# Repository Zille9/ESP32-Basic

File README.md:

# ESP32-Basic with FabGL VGA library + PS2-Keyboard
### Basic32+ with FabGL VGA library + PS2 PS2Controller for VGA monitor output - 2019 - 2023       
#### Ursprungsversion von: Rob Cai <rocaj74@gmail.com>
#### erweitert/modifiziert von:Reinhard Zielinski <zille09@gmail.com>                                                                   
#### Das Ergebnis ist ein kleiner Retro-Computer mit folgender Ausstattung:
- (Schaltplan siehe Ordner Schematic) 

## Hardware:
```
-ESP32 / 240MHz
-56472 Basic Bytes free
-VGA-Display 320x240 Pixel 64 Farben , AV (IO26) oder TFT-Screen 320x240 Pixel
-IO-Erweiterung mit MCP23017 (2x8 IO-Ports) + EEPROM 512kB 
-CardKb als PS2-Tastatur nutzbar (siehe Ordner <src/CardKeyBoard_neu>)
-Unterstützung von externem SPI-RAM 128kB, 512kB (Adafruit SPI-Fram) oder 2, 4 oder 8 MB PSRAM im SPI-Mode
-PS2-Keyboard 
-RTC DS3231 
-SD-Card
```

## Software:
```
Die Ursprungsversion wurde durch folgende Funktionen erweitert  

-fliesskomma Arithmetik
-Grafikfunktionen 	
-mathematische Funktionen 	
-Stringfunktionen 	
-lange Variablennamen  	
-viele zusätzliche Befehle (DATA,READ,STRG$,LEFT$,RIGHT$,MID$,POS,TAB,SPC,SIN,COS,TAN,ATN,LOG,SQR,PI usw.) 	
-erweiterte logische Operatoren (AND, OR) 	
-BIT-Manipulation &,|,%,<<,>> usw. 	
-Klammerrechnung 	
-IF THEN ELSE Abfragen 	
-Speichermonitor 	
-Exponential-Ein/Ausgabe 	
-Verschiedene Sensoren und Komponenten HC-S04, Dallas DS18S20, DHT, LCD, Neopixel-LED, BMP180 	
-Zeileneditor 
-BMP-Bilddatei-Import / Export
-Spritefunktionen (noch in der Entwicklung)
-Soundfunktionen (noch in der Entwicklung)
-integrierte Kurzhilfe
-Binärprogramme können mit RUN"/xxx.bin" gestartet werden - siehe Ordner <Software>

```

***Special Thanks on Guido Lehwalder and Marcelo Dantas ->RUN-CPM is a great Work!***

***Also thanks on Fabrizio Di Vittorio for the excellent FabGl-Library***

```
-Startbildschirm
```

```
-Basic-Befehle
```

```
-Basic -Funktionen
```

```
-Programm Globus.Bas
```

```
-Darstellung einer BMP-Datei
```

```
-Programmlisting
```

```
Screenshot als BMP-Datei exportiert
```

```
...mit RUN kann dann auch CPM gestartet werden.
```

```
...RUN-CPM Startbildschirm , mit EXIT kehrt man wieder zum Basic32+ zurück.
```

```
...der GRID-Befehl in Aktion .
```

## Bibliotheken einbinden und Basic32+ compilieren:
```
-die im Ordner libraries liegenden Unterverzeichnisse ins Arduino libraries-Verzeichnis kopieren

-zusätzlich die FabGL-lib mit dem Bibliotheksmanager der Arduino-IDE installieren

-die Quellen befinden sich im Ordner "src/FabGL-Basic" ->kompilieren und in den ESP32 laden

-den Inhalt des Verzeichnisses SD-Card auf eine SD-Karte kopieren .... und mit ESP32+Basic loslegen :-)

Im Ordner RUN-CPM befindet sich die um den OTA-Loader erweiterte Variante, um nach Eingabe von EXIT wieder zum Basic zurückzukehren.
```

## Komponenten:

-ESP32 NodeMCU https://www.berrybase.de/esp32-nodemcu-development-board?sPartner=g_shopping&gclid=EAIaIQobChMI-fTJwNmx_wIVkupRCh1mTAgZEAQYBSABEgKjwvD_BwE

-MCP23017 https://www.reichelt.de/i-o-erweiterung-16bit-1-8-5v-seriell-i2c-dip-28-mcp-23017-e-sp-p140074.html?&trstct=pos_0&nbc=1

-FRAM 512kB https://www.adafruit.com/product/4719

-SD-Card Modul https://www.reichelt.de/arduino-sd-karten-modul-ard-module-sd-p282683.html?PROVID=2788&gclid=EAIaIQobChMIqL3-sdqx_wIVQ9rVCh1oSQiAEAQYAiABEgL9BPD_BwE

-RTC-Modul https://www.reichelt.de/entwicklerboards-praezisions-echtzeituhr-ds3231-debo-rtc-uhr2-p235506.html?PROVID=2788&gclid=EAIaIQobChMImaDrzNqx_wIVQs7VCh1VowhwEAQYBCABEgLQoPD_BwE

-siehe auch BOOM-List im Ordner Schematic ->folgt bald

 ### Author:Reinhard Zielinski <zille09@gmail.com> April 2021

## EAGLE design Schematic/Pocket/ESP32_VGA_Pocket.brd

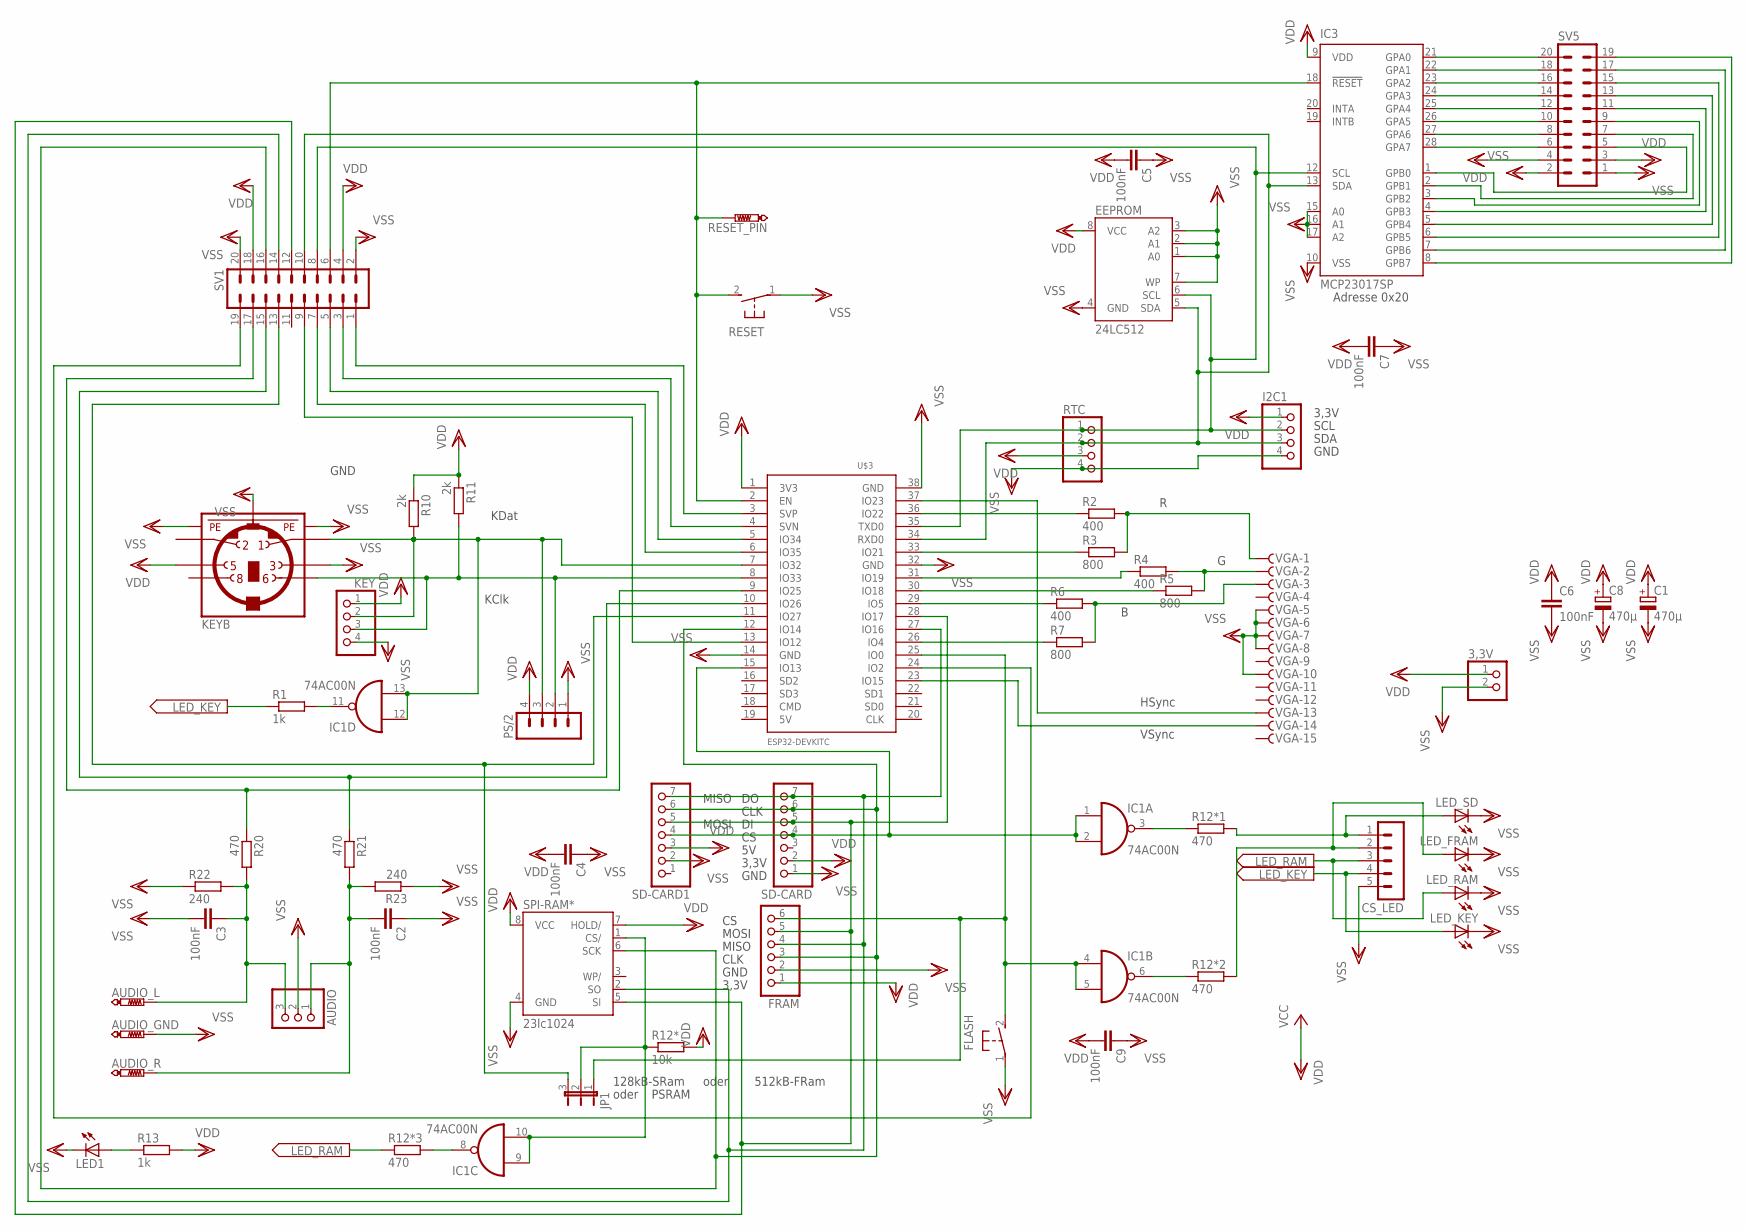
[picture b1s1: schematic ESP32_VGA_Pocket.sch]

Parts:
3,3V: PINHD-1X2; 1X02
AUDIO: PINHD-1X3; 1X03
AUDIO_GND: PTR1PAD1-13Y; P1-13Y
AUDIO_L: PTR1PAD1-13Y; P1-13Y
AUDIO_R: PTR1PAD1-13Y; P1-13Y
C1, C8: 470µ; E3,5-10
C2, C3, C4, C5, C6, C7, C9: 100nF; C025-030X050
CS_LED: MA05-1
EEPROM: 24LC512; DIL08
FLASH: 31-XX; B3F-31XX; MPN B3F-3100
FRAM: PINHD-1X6; 1X06
I2C1: PINHD-1X4; 1X04
IC1: 74AC00N; DIL14
IC3: MCP23017SP; DIL28-3; MPN MCP23017-E/SO
JP1: JP2E; JP2
KEY: PINHD-1X4; 1X04
KEYB: MINI_DIN_6; M_DIN6
LED1: LED5MM
LED_FRAM: LED5MM
LED_KEY: LED5MM
LED_RAM: LED5MM
LED_SD: LED5MM
PS/2: MA04-1
R1, R13: 1k; 0204/7
R2, R4, R6: 400; 0204/7
R3, R5, R7: 800; 0204/7
R10, R11: 2k; 0204/7
R12*: 10k; 0204/7
R12*1, R12*2, R12*3, R20, R21: 470; 0204/7
R22, R23: 240; 0204/7
RESET: 31-XX; B3F-31XX
RESET_PIN: PTR1PAD1-17Y; P1-17Y
RTC: PINHD-1X4; 1X04
SD-CARD, SD-CARD1: PINHD-1X7; 1X07
SPI-RAM*: 23lc1024; DIL08
SV1, SV5: MA10-2
U$3: ESP32DEVKITC; ESP32-DEVKITC
VGA: F15HDHS; HDF15H

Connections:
AUDIO1: AUDIO.3, AUDIO_L.TP, C3.1, R20.2, R22.2
AUDIO2: AUDIO.1, AUDIO_R.TP, C2.2, R21.2, R23.2
CLK: FRAM.3, SD-CARD.6, SD-CARD1.6, SPI-RAM*.6 (SCK), SV1.16, U$3.12 (IO14)
CLK_K: KEY.3, KEYB.6, PS/2.2, R11.2, U$3.8 (IO33)
CS_RAM: IC1.9 (I0), IC1.10 (I1), JP1.2, R12*.1, SPI-RAM*.1 (CS/)
CS_SD: IC1.1 (I0), IC1.2 (I1), SD-CARD.4, SD-CARD1.4, U$3.15 (IO13)
DAT_K: IC1.12 (I0), IC1.13 (I1), KEY.2, KEYB.1, PS/2.3, R10.2, U$3.7 (IO32)
FLASH: FLASH.2 (S), FRAM.6, IC1.4 (I0), IC1.5 (I1), JP1.1, U$3.25 (IO0)
GND: IC1.7 (GND)
IO2: SV1.19, U$3.24 (IO2)
IO12: SV1.9, U$3.13 (IO12)
IO27: JP1.3, SV1.13, U$3.11 (IO27)
IO34: SV1.5, U$3.5 (IO34)
IO35: SV1.7, U$3.6 (IO35)
IO36: SV1.1, U$3.3 (SVP)
IO39: SV1.3, U$3.4 (SVN)
LED_FRAM: CS_LED.2, LED_FRAM.A, R12*2.2
LED_KEY: CS_LED.4, LED_KEY.A, R1.1
LED_RAM: CS_LED.3, LED_RAM.A, R12*3.1
LED_SD: CS_LED.1, LED_SD.A, R12*1.2
MISO: FRAM.4, SD-CARD.7, SD-CARD1.7, SPI-RAM*.2 (SO), SV1.14, U$3.27 (IO16)
MOSI: FRAM.5, SD-CARD.5, SD-CARD1.5, SPI-RAM*.5 (SI), SV1.12, U$3.28 (IO17)
unnamed: R20.1, SV1.17, U$3.9 (IO25)
unnamed: IC1.3 (O), R12*1.1
unnamed: R21.1, SV1.15, U$3.10 (IO26)
unnamed: IC1.11 (O), R1.2
unnamed: IC1.6 (O), R12*2.1
unnamed: IC1.8 (O), R12*3.2
unnamed: LED1.A, R13.1
unnamed: IC3.1 (GPB0), SV5.5
unnamed: IC3.21 (GPA0), SV5.20
unnamed: IC3.22 (GPA1), SV5.18
unnamed: IC3.23 (GPA2), SV5.16
unnamed: IC3.24 (GPA3), SV5.14
unnamed: IC3.25 (GPA4), SV5.12
unnamed: IC3.26 (GPA5), SV5.10
unnamed: IC3.27 (GPA6), SV5.8
unnamed: IC3.28 (GPA7), SV5.6
unnamed: IC3.2 (GPB1), SV5.7
unnamed: IC3.3 (GPB2), SV5.9
unnamed: IC3.4 (GPB3), SV5.11
unnamed: IC3.5 (GPB4), SV5.13
unnamed: IC3.6 (GPB5), SV5.15
unnamed: IC3.7 (GPB6), SV5.17
unnamed: IC3.8 (GPB7), SV5.19
unnamed: R6.2, R7.2, VGA.3
unnamed: R4.2, R5.2, VGA.2
unnamed: R2.2, R3.2, VGA.1
unnamed: R2.1, U$3.36 (IO22)
unnamed: R3.1, U$3.33 (IO21)
unnamed: R4.1, U$3.31 (IO19)
unnamed: R5.1, U$3.30 (IO18)
unnamed: R6.1, U$3.29 (IO5)
unnamed: R7.1, U$3.26 (IO4)
unnamed: U$3.37 (IO23), VGA.13
unnamed: U$3.23 (IO15), VGA.14
RESET: IC3.18 (!RESET), RESET.2 (S), RESET_PIN.TP, SV1.6, U$3.2 (EN)
SCL: EEPROM.6 (SCL), I2C1.2, IC3.12 (SCL), RTC.1, SV1.8, U$3.35 (TXD0)
SDA: EEPROM.5 (SDA), I2C1.3, IC3.13 (SDA), RTC.2, SV1.10, U$3.34 (RXD0)
VDD: 3,3V.1, C1.+, C4.2, C5.2, C6.1, C7.2, C8.+, C9.2, EEPROM.8 (VCC), FRAM.1, I2C1.1, IC1.14 (VCC), IC3.9 (VDD), KEY.1, KEYB.5, PS/2.4, R10.1, R11.1, R12*.2, R13.2, RTC.3, SD-CARD.2, SD-CARD1.3, SPI-RAM*.7 (HOLD/), SPI-RAM*.8 (VCC), SV1.4, SV1.18, SV5.3, SV5.4, U$3.1 (3V3)
VSS: 3,3V.2, AUDIO.2, AUDIO_GND.TP, C1.-, C2.1, C3.2, C4.1, C5.1, C6.2, C7.1, C8.-, C9.1, CS_LED.5, EEPROM.1 (A0), EEPROM.2 (A1), EEPROM.3 (A2), EEPROM.4 (GND), EEPROM.7 (WP), FLASH.1, FRAM.2, I2C1.4, IC3.10 (VSS), IC3.15 (A0), IC3.16 (A1), IC3.17 (A2), KEY.4, KEYB.3, KEYB.SH1 (PE1), KEYB.SH2 (PE2), KEYB.SH3 (PE3), LED1.K (C), LED_FRAM.K (C), LED_KEY.K (C), LED_RAM.K (C), LED_SD.K (C), PS/2.1, R22.1, R23.1, RESET.1, RTC.4, SD-CARD.1, SD-CARD1.2, SPI-RAM*.4 (GND), SV1.2, SV1.20, SV5.1, SV5.2, U$3.14 (GND), U$3.32 (GND), U$3.38 (GND), VGA.5, VGA.6, VGA.7, VGA.8, VGA.10

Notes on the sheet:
CLK
MISO
MOSI
KDat
KClk
VSync
HSync
GND
SCL
SDA
3,3V
128kB-SRam
512kB-FRam
oder
Adresse 0x20
PSRAM

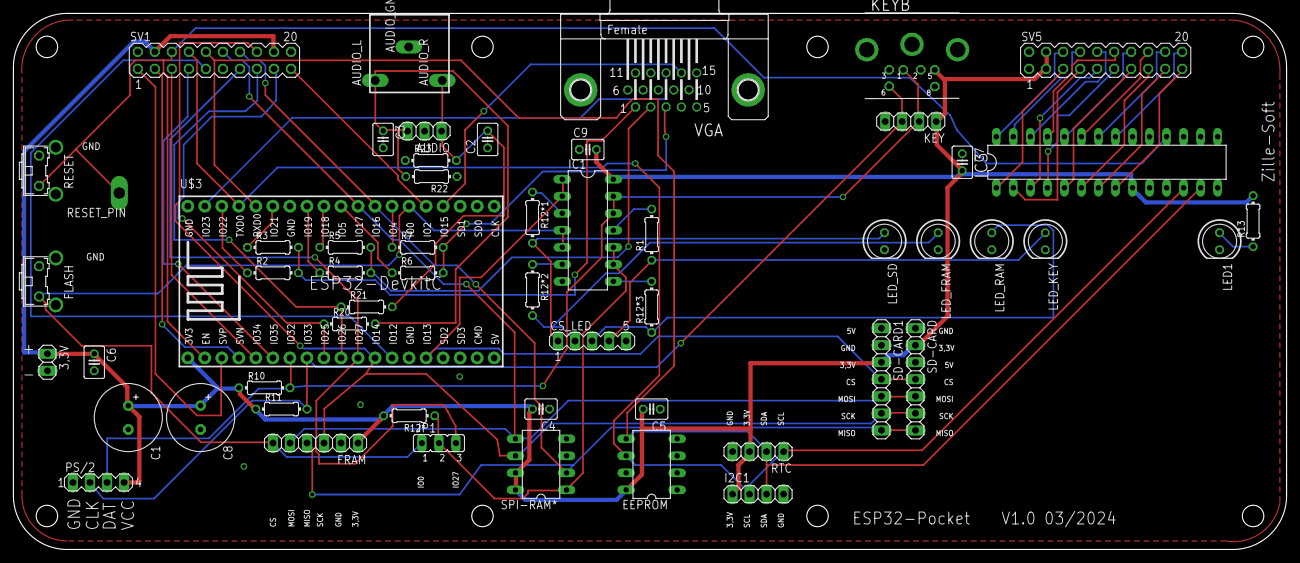
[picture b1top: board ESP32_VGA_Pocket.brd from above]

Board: 2 copper layers, 190.0 x 80.0 mm, 58 parts (0 on the bottom side), 60 nets.

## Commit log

2024-03-30 add volume control
2024-03-30 playorder incorrect
2024-03-31 Korrektur ARC-Befehl
2024-04-05 add cardkb_ps2 keyboard
2024-04-05 Schematic update
2024-04-07 update CardKeyBoard_neu
2024-04-07 update Images
2024-04-12 add Ctrl-Function in CardKB
2024-05-17 update DIR-Command
